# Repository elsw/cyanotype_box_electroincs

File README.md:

# cyanotype_box_electronics

This is project for use with creating cyanotypes using high power UV LEDs.

These PCBS are designed to control the exposure time and intensity using a LCB screen and keypad

## PCBs

The PCBs are split into 2 parts, control box and light board.

Once control box can support up to 10 light boards daisy chained together

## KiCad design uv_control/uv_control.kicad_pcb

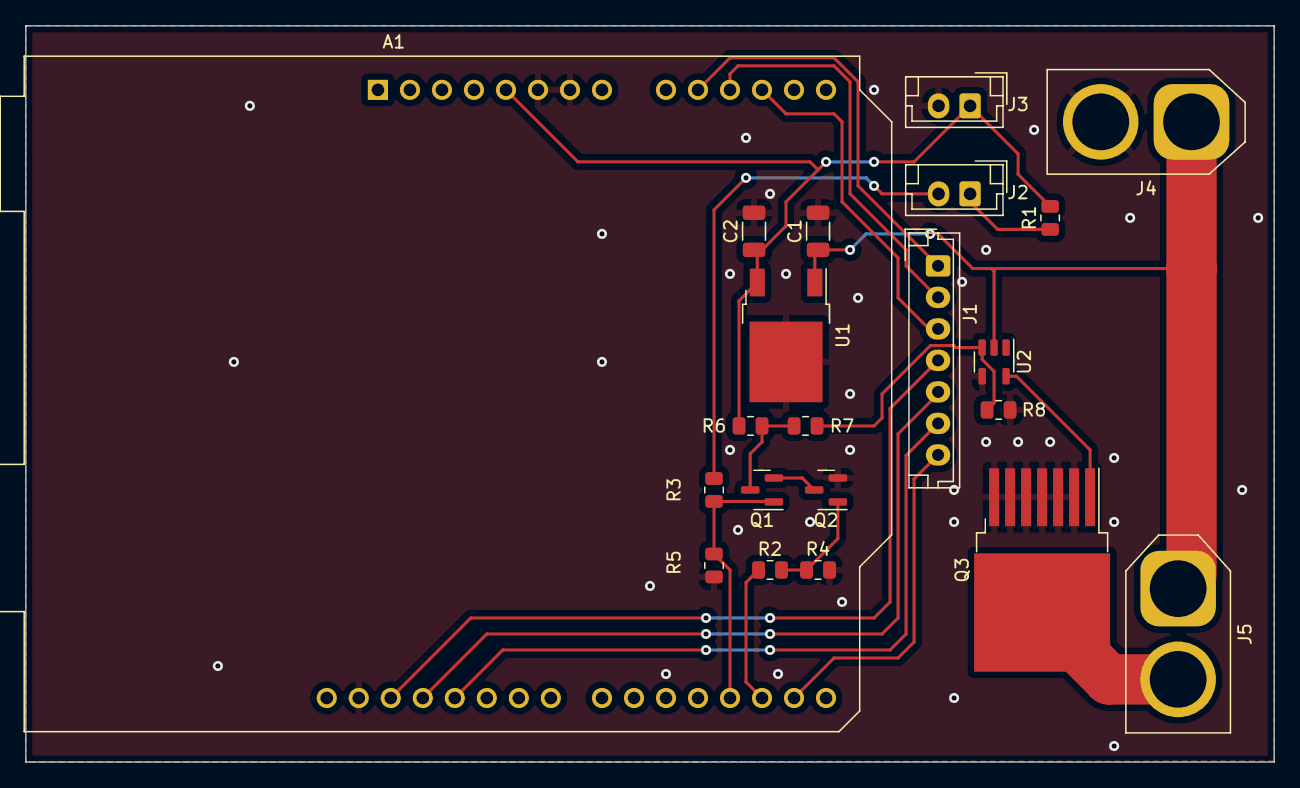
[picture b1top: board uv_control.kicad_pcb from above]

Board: 2 copper layers, 99.1 x 58.4 mm, 21 parts (0 on the bottom side), 20 nets.

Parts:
A1: Arduino_UNO_R2
C1, C2: 100nf; C_1206_3216Metric
J1: Keypad; JST_EH_B7B-EH-A_1x07_P2.50mm_Vertical
J2: Safety; JST_EH_B2B-EH-A_1x02_P2.50mm_Vertical
J3: Fan; JST_EH_B2B-EH-A_1x02_P2.50mm_Vertical
J4: 12V Power; AMASS_XT60-M_1x02_P7.20mm_Vertical
J5: Light Power; AMASS_XT60-F_1x02_P7.20mm_Vertical
Q1, Q2: BSS138; SOT-23
Q3: IRFS7730-7; TO-263-7_TabPin8
R1, R2, R3, R7: 100R; R_0805_2012Metric
R4, R5, R8: 10K; R_0805_2012Metric
R6: 1k; R_0805_2012Metric
U1: L7805; TO-252-2
U2: MCP1415; SOT-23-5

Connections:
+5V: A1.5 (+5V), C2.1, J3.1, R1.2, R6.1, U1.3 (OUT)
+12V: C1.1, J4.1, J5.1, U1.1 (IN), U2.2 (Vdd)
/Keypad_1: A1.10 (A1), J1.1
/Keypad_2: A1.11 (A2), J1.2
/Keypad_3: A1.12 (A3), J1.3
/safety: A1.18 (D3), Q1.1 (G), R3.2, R5.1
GND: A1.6 (GND), A1.7 (GND), A1.29 (GND), C1.2, C2.2, J3.2, J4.2, Q2.2 (S), Q3.2 (S), Q3.3 (S), Q3.4 (S), Q3.5 (S), Q3.6 (S), Q3.7 (S), R4.2, R5.2, R8.2, U1.2 (GND), U2.4 (GND)
unnamed: A1.16 (D1/TX), J1.7
unnamed: A1.17 (D2), R2.1
unnamed: A1.26 (D11), J1.6
unnamed: A1.27 (D12), J1.5
unnamed: A1.28 (D13), J1.4
unnamed: J2.1, R1.1
unnamed: J2.2, R3.1
unnamed: J5.2, Q3.8 (D)
unnamed: Q1.2 (S), Q2.3 (D)
unnamed: Q1.3 (D), R6.2, R7.1
unnamed: Q2.1 (G), R2.2, R4.1
unnamed: Q3.1 (G), U2.5 (~OUT)
unnamed: R7.2, R8.1, U2.3 (IN)

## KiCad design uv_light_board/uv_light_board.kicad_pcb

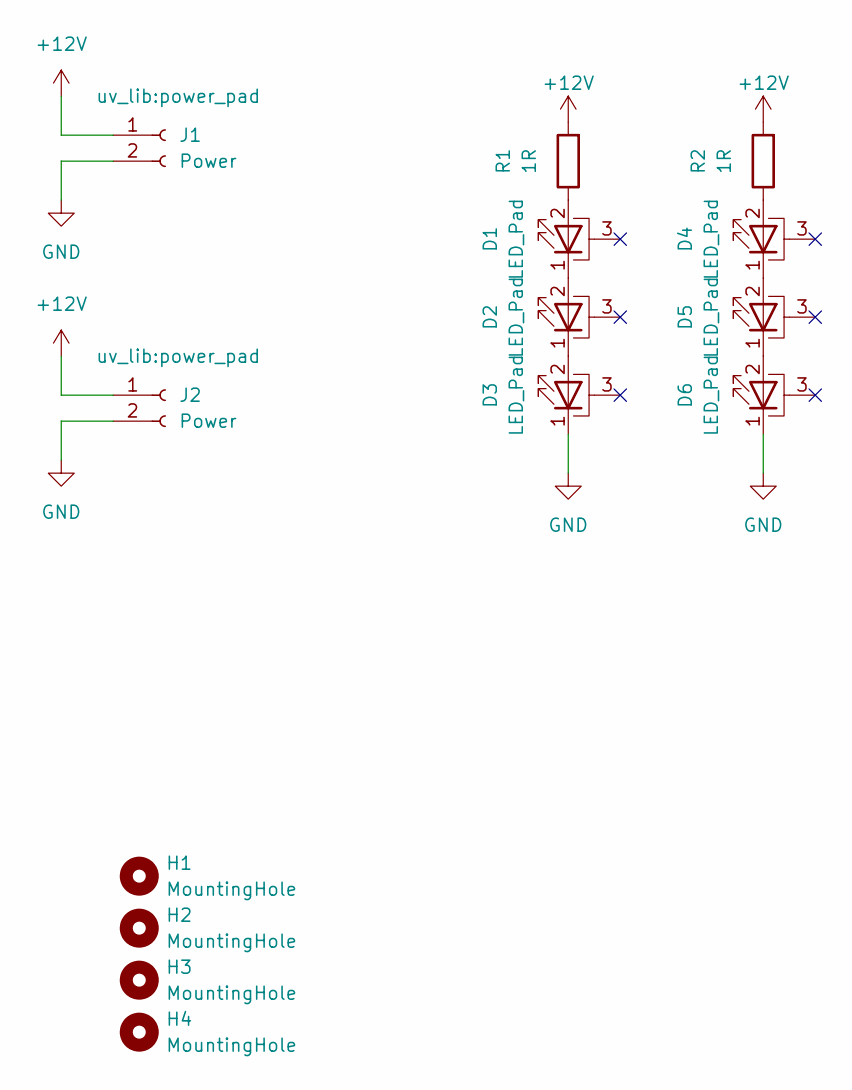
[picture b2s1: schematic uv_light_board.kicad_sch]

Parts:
D1, D2, D3, D4, D5, D6: LED_Pad; LED_1W_3W_R8
H1, H2, H3, H4: MountingHole; MountingHole_3.2mm_M3
J1, J2: Power; power_pad
R1, R2: 1R; R_2512_6332Metric

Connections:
+12V: J1.1, J2.1, R1.2, R2.2
GND: D3.1 (K), D6.1 (K), J1.2, J2.2
unnamed: D1.1 (K), D2.2 (A)
unnamed: D1.2 (A), R1.1
unnamed: D2.1 (K), D3.2 (A)
unnamed: D4.1 (K), D5.2 (A)
unnamed: D4.2 (A), R2.1
unnamed: D5.1 (K), D6.2 (A)

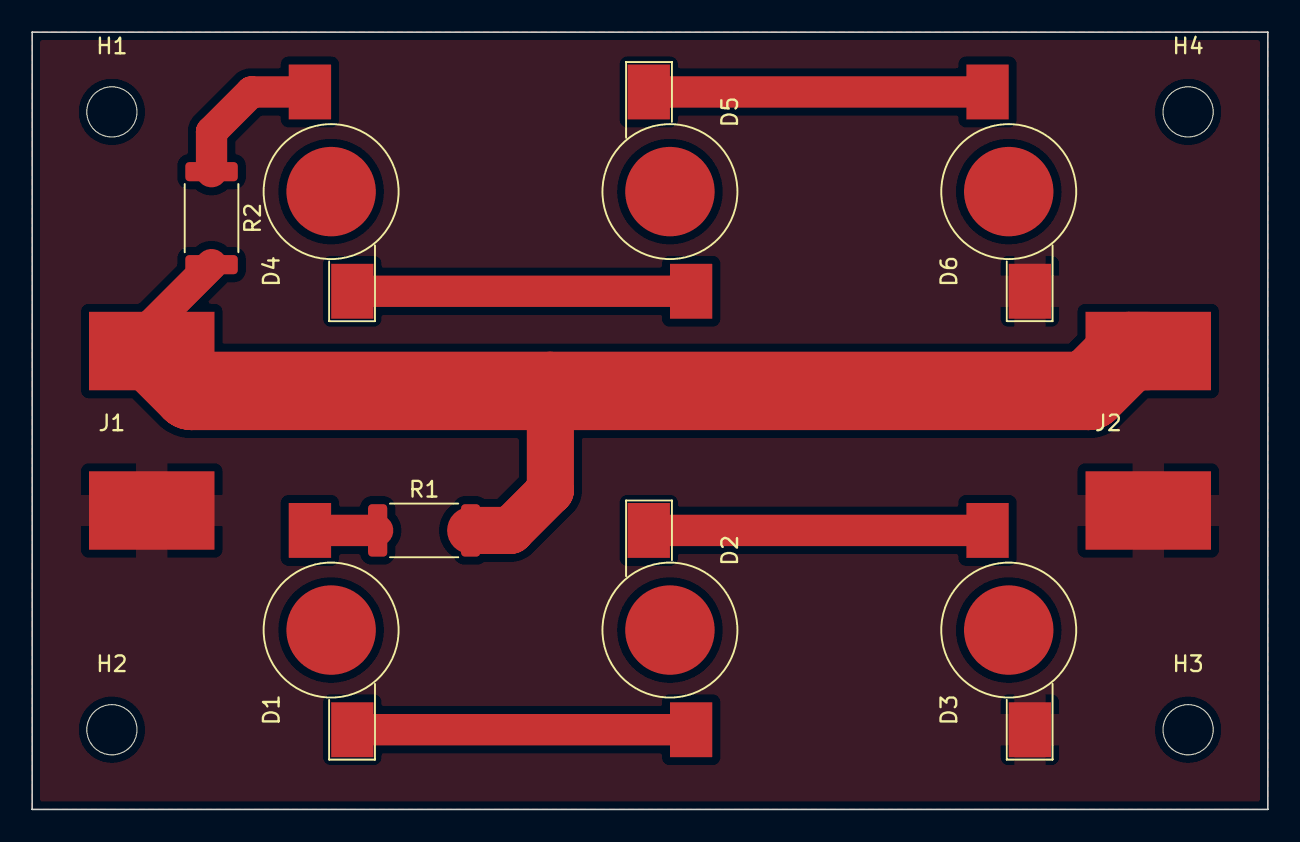
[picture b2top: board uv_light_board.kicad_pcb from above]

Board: 2 copper layers, 78.7 x 49.5 mm, 14 parts (0 on the bottom side), 8 nets.

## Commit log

2022-10-07 Adding initial PCBs
2022-10-16 Updating control board to include more pinouts
2022-10-31 Adding arduino code
    Added BOM spreadsheet
2022-11-05 Updated wiring to avoid Serial debug port
2022-11-05 Refactoring states to individual classes
2022-11-11 Add lcd output
2022-11-11 Updating pinout
2022-11-13 Updating PCB to change to 2 layer setup
    Added LCD schematic, removing LCD shield design
    Fixed XT60 polarity
    Added Status LED and Safety LED
2022-11-15 Updating arduino code
2022-11-15 Reverting to V1 PCB in main branch
2022-11-16 removed debug output
2022-11-26 fixing bugs in uv control code
2024-02-05 Changing v2 to a RP2040 based solution
